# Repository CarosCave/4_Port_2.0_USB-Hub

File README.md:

# 4_Port_2.0_USB-Hub
I made a 4 port 2.0 USB-Hub with an exar XR22404 Chip. I wanted to test the schematic for the USB-Chip to use it in a further project. Version 1 is up and running here. But the costs for one complete equipped PCB is about 60€. Now in V2.0 I decreased the costs to 28€ for the parts.

You will find the:
-  CAD-Files in the folder **KiCAD**
-  The manufacturing files in the folder **Gerber-files**
-  The PDF documents in the folder **PDF**
-  The licence files from CERN OHL v. 1.2 under **Licence**

Or you order the complete Project by my friends from Aisler B.V.. The will deliver the complete project incl. all parts (excl. the USB-Chip from Exar). You'll find the project under the following link:
https://aisler.net/DK1CMB/4-port-2-0-usb-hub/main-pcb

The USB-Chip is an Exar XR22404CG28TR-F.

## Licence:  
**Copyright Caroline Brix 2017.**  
This documentation describes Open Hardware and is licensed under the CERN OHL v. 1.2.
You may redistribute and modify this documentation under the terms of the CERN OHL v.1.2. (http://ohwr.org/cernohl). This documentation is distributed WITHOUT ANY EXPRESS OR IMPLIED WARRANTY, INCLUDING OF MERCHANTABILITY, SATISFACTORY QUALITY AND FITNESS FOR A PARTICULAR PURPOSE. Please see the CERN OHL v.1.2 for applicable conditions

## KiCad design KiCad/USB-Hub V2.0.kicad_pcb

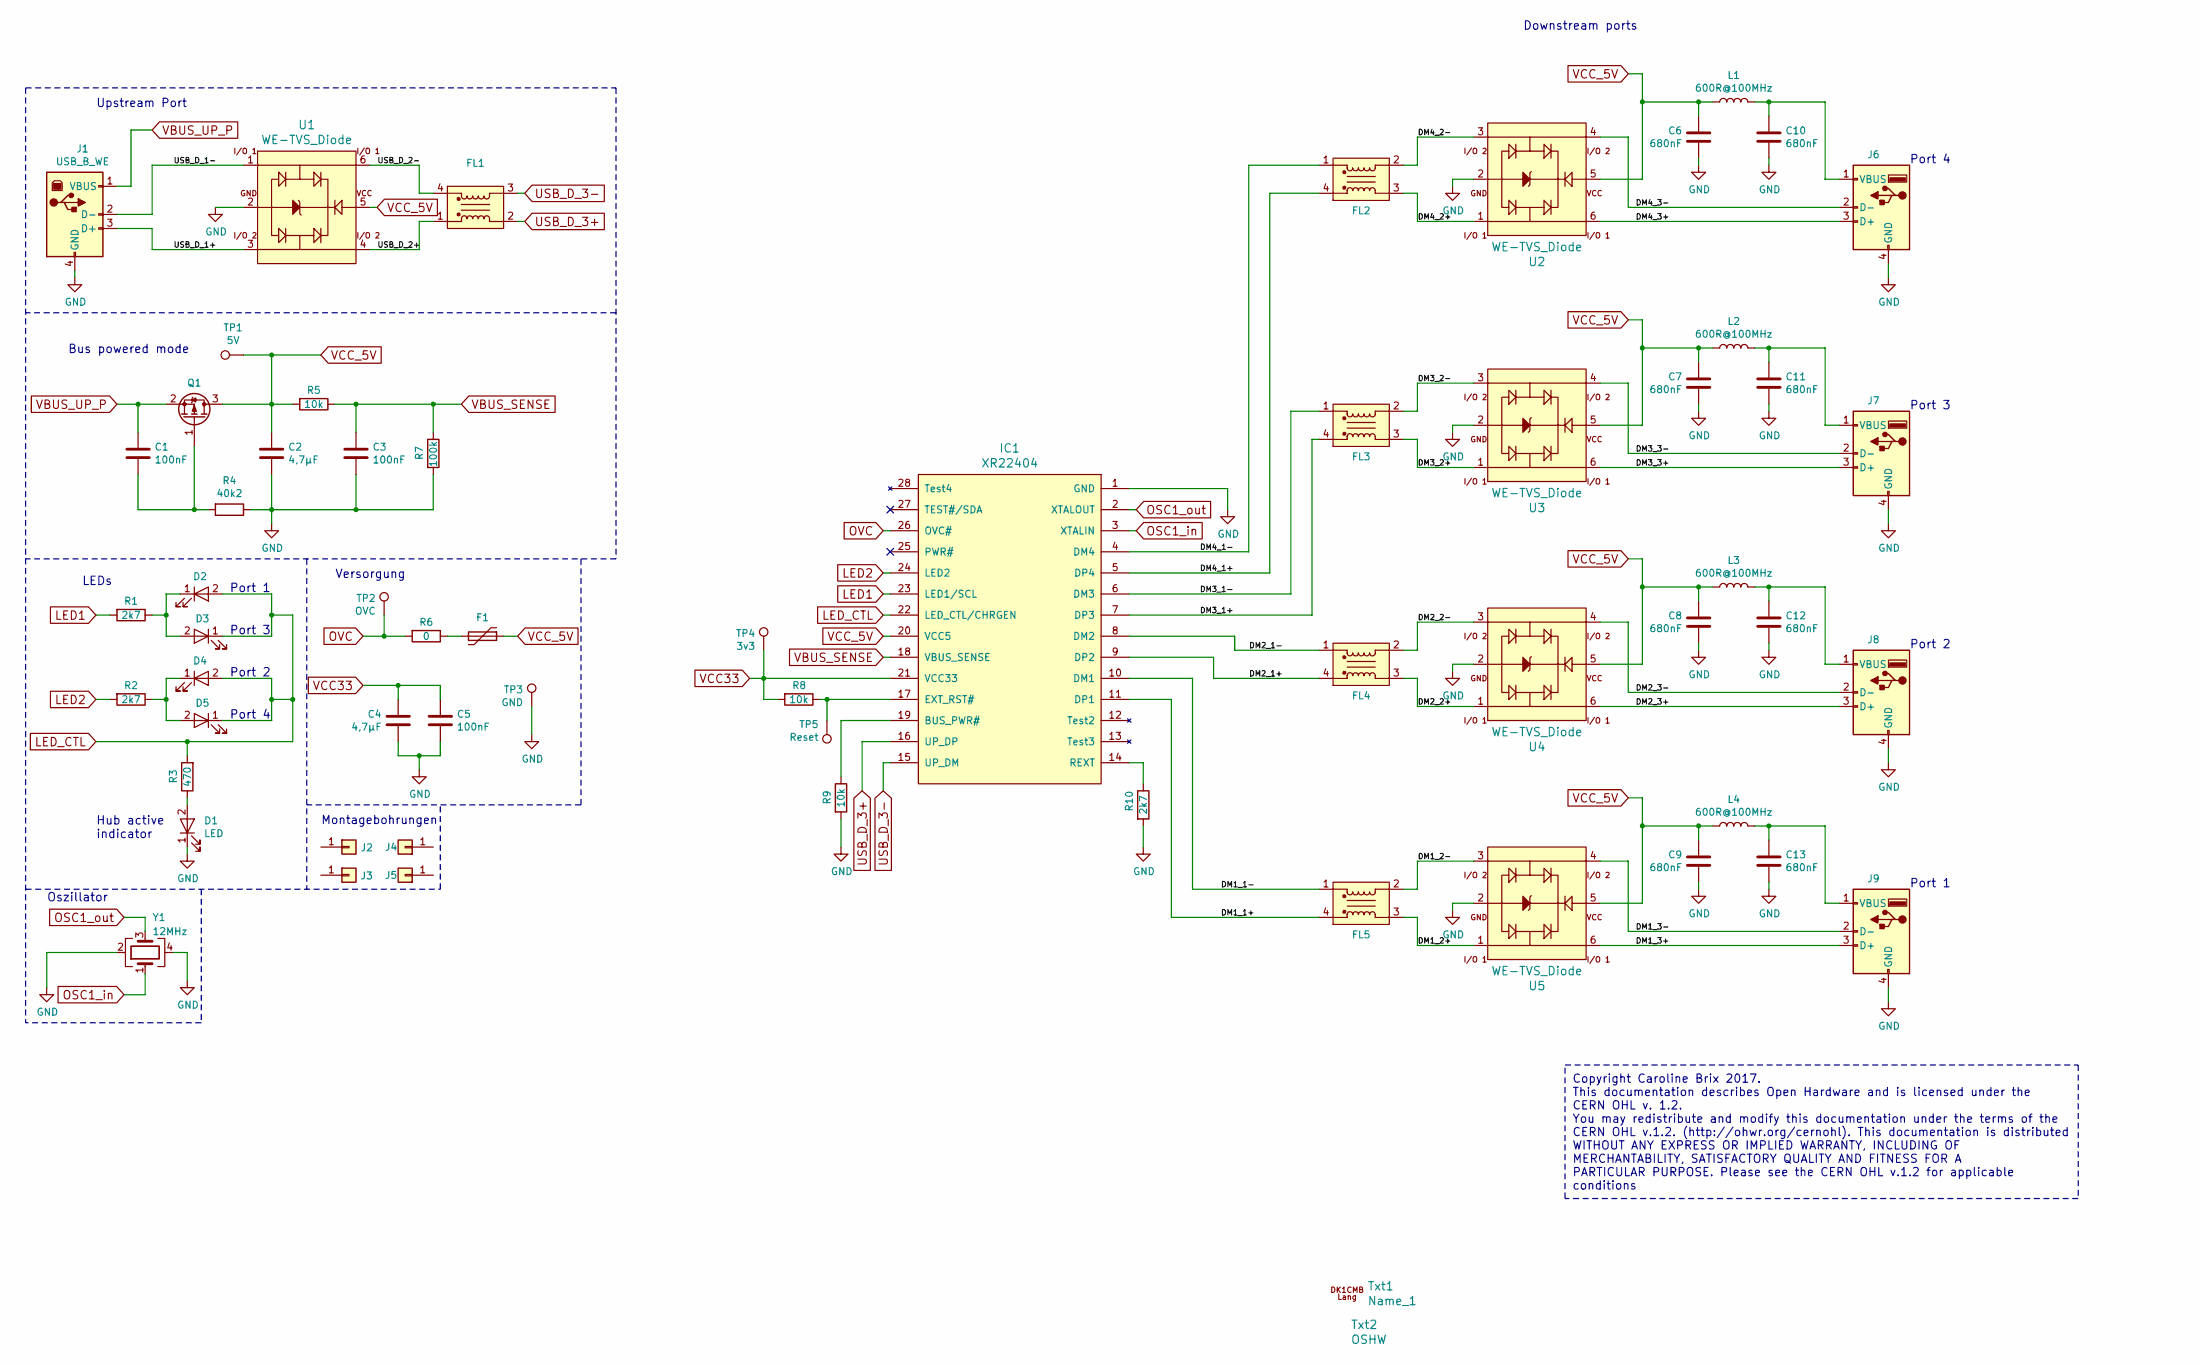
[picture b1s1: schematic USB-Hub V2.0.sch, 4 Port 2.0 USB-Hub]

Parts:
C1, C3, C5: 100nF; R_0805_HandSoldering
C2, C4: 4,7µF; R_0805_HandSoldering
C6, C7, C8, C9, C10, C11, C12, C13: 680nF; R_0805_HandSoldering
D1, D2, D3, D4, D5: LED; LED_0805_HandSoldering
F1: Polyfuse; R_1206_HandSoldering
FL1, FL2, FL3, FL4, FL5: EMI_Common_Mode_Line_Filter; WE-CNSW
IC1: XR22404
J1: USB_B_WE; USB_B_THT_WE
J2, J3, J4, J5: Conn_01x01; MountingHole_3.2mm_M3_Pad
J6, J7, J8, J9: USB_A_shielded; USB_A_shielded_WE
L1, L2, L3, L4: 600R@100MHz; R_0805_HandSoldering
Q1: NTR2101P; SOT-23
R1, R2, R10: 2k7; R_0805_HandSoldering
R3: 470; R_0805_HandSoldering
R4: 40k2; R_0805_HandSoldering
R5, R8, R9: 10k; R_0805_HandSoldering
R6: 0; R_0805_HandSoldering
R7: 100k; R_0805_HandSoldering
TP1: 5V; Test_Point_Pad_d3.0mm
TP2: OVC; Test_Point_Pad_d3.0mm
TP3: GND; Test_Point_Pad_d3.0mm
TP4: 3v3; Test_Point_Pad_d3.0mm
TP5: Reset; Test_Point_Pad_d3.0mm
Txt1: Name_1; Name_Lang
Txt2: OSHW; OSHW-Logo2_7.3x6mm_SilkScreen
U1, U2, U3, U4, U5: WE-TVS_Diode; SOT23-6L
Y1: 12MHz; Crystal_SMD_3225-4pin_3.2x2.5mm_HandSoldering

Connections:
/DM1_1+: FL5.4, IC1.11 (DP1)
/DM1_1-: FL5.1, IC1.10 (DM1)
/DM1_2+: FL5.3, U5.1
/DM1_2-: FL5.2, U5.3
/DM1_3+: J9.3 (D+), U5.6
/DM1_3-: J9.2 (D-), U5.4
/DM2_1+: FL4.4, IC1.9 (DP2)
/DM2_1-: FL4.1, IC1.8 (DM2)
/DM2_2+: FL4.3, U4.1
/DM2_2-: FL4.2, U4.3
/DM2_3+: J8.3 (D+), U4.6
/DM2_3-: J8.2 (D-), U4.4
/DM3_1+: FL3.4, IC1.7 (DP3)
/DM3_1-: FL3.1, IC1.6 (DM3)
/DM3_2+: FL3.3, U3.1
/DM3_2-: FL3.2, U3.3
/DM3_3+: J7.3 (D+), U3.6
/DM3_3-: J7.2 (D-), U3.4
/DM4_1+: FL2.4, IC1.5 (DP4)
/DM4_1-: FL2.1, IC1.4 (DM4)
/DM4_2+: FL2.3, U2.1
/DM4_2-: FL2.2, U2.3
/DM4_3+: J6.3 (D+), U2.6
/DM4_3-: J6.2 (D-), U2.4
/USB_D_1+: J1.3 (D+), U1.3
/USB_D_1-: J1.2 (D-), U1.1
/USB_D_2+: FL1.1, U1.4
/USB_D_2-: FL1.4, U1.6
GND: C2.2, C3.2, C4.1, C5.2, C6.1, C7.1, C8.1, C9.1, C10.2, C11.2, C12.2, C13.2, D1.1 (K), IC1.1 (GND), J1.4 (GND), J6.4 (GND), J7.4 (GND), J8.4 (GND), J9.4 (GND), R4.1, R7.2, R9.2, R10.2, TP3.1, U1.2, U2.2, U3.2, U4.2, U5.2, Y1.2, Y1.4
LED1: IC1.23 (LED1/SCL), R1.2
LED2: IC1.24 (LED2), R2.2
LED_CTL: D2.2 (A), D3.1 (K), D4.2 (A), D5.1 (K), IC1.22 (LED_CTL/CHRGEN), R3.2
unnamed: C1.2, Q1.1 (G), R4.2
unnamed: C10.1, J6.1 (VBUS), L1.2
unnamed: C11.1, J7.1 (VBUS), L2.2
unnamed: C12.1, J8.1 (VBUS), L3.2
unnamed: C13.1, J9.1 (VBUS), L4.2
unnamed: D1.2 (A), R3.1
unnamed: D2.1 (K), D3.2 (A), R1.1
unnamed: D4.1 (K), D5.2 (A), R2.1
unnamed: F1.2, R6.1
unnamed: IC1.14 (REXT), R10.1
unnamed: IC1.17 (EXT_RST#), R8.1, TP5.1
unnamed: IC1.19 (BUS_PWR#), R9.1
OSC1_in: IC1.3 (XTALIN), Y1.1
OSC1_out: IC1.2 (XTALOUT), Y1.3
OVC: IC1.26 (OVC#), R6.2, TP2.1
USB_D_3+: FL1.2, IC1.16 (UP_DP)
USB_D_3-: FL1.3, IC1.15 (UP_DM)
VBUS_SENSE: C3.1, IC1.18 (VBUS_SENSE), R5.1, R7.1
VBUS_UP_P: C1.1, J1.1 (VBUS), Q1.2 (S)
VCC33: C4.2, C5.1, IC1.21 (VCC33), R8.2, TP4.1
VCC_5V: C2.1, C6.2, C7.2, C8.2, C9.2, F1.1, IC1.20 (VCC5), L1.1, L2.1, L3.1, L4.1, Q1.3 (D), R5.2, TP1.1, U1.5, U2.5, U3.5, U4.5, U5.5

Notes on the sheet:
Bus powered mode
Port 1
Port 3
Port 2
Port 4
LEDs
Hub active indicator
Oszillator
Versorgung
Downstream ports
Port 3
Montagebohrungen
Upstream Port
Copyright Caroline Brix 2017. This documentation describes Open Hardware and is licensed under the CERN OHL v. 1.2. You may redistribute and modify this documentation under the terms of the CERN OHL v.1.2. (http://ohwr.org/cernohl). This documentation is distributed WITHOUT ANY EXPRESS OR IMPLIED W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

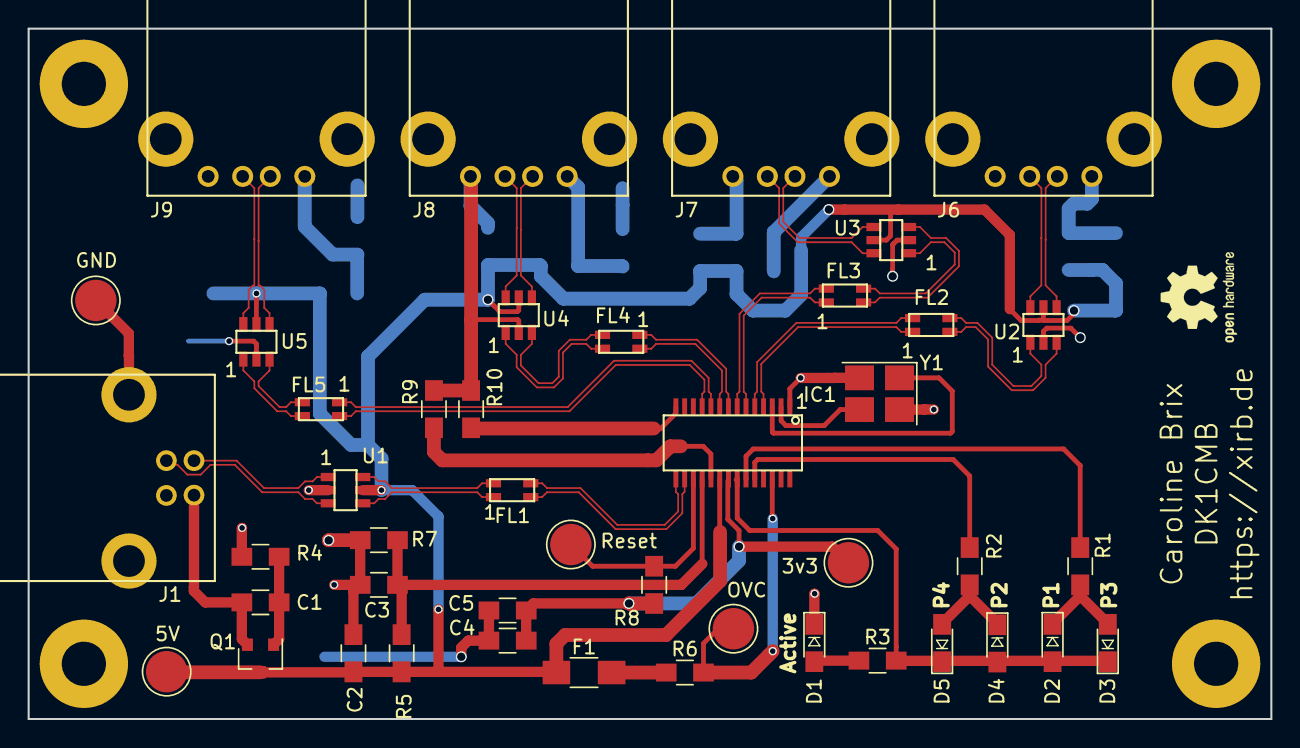
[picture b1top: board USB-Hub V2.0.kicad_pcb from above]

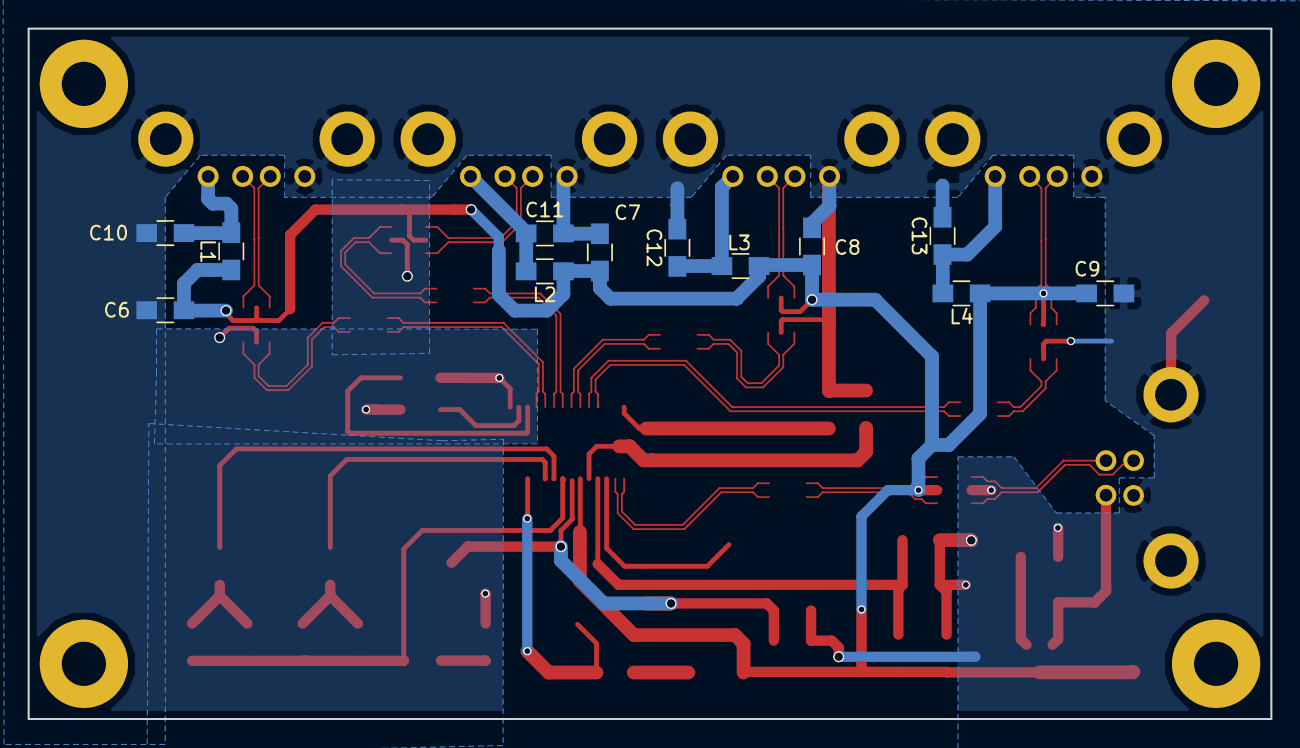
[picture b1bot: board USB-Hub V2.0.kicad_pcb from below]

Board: 2 copper layers, 90.0 x 50.0 mm, 62 parts (12 on the bottom side), 53 nets.

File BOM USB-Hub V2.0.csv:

ID;Bezeichner;Gehäuse;Stückzahl;Bezeichnung;Hersteller;Hersteller-Teilenummer;Mouser-Bestellnummer;Digikey-Bestellnummer;Preis Mouser;;Preis Digikey;;Datenblatt;Identifier;Case;Pieces;Description;Manufacturer;Manufacturer part number;Mouser part number;Digikey part number;Costs Mouser;;Costs Digikey;;Datasheet1;IC1;SSOP-28;1;USB-IC USB 2.0 4-Port Hub;Exar;XR22404CG28TR-F;701-XR22404CG28TR-F;nA; 2,02 € ; 2,02 € ;; -   € ;http://www.mouser.com/ds/2/146/XR22404-1006299.pdf2;J1;USB B;1;USB_B_WE;Wurth;61400416121;710-61400416121;732-2108-ND; 1,20 € ; 1,20 € ; 1,20 € ; 1,20 € ;http://katalog.we-online.de/em/datasheet/61400416121.pdf3;J6,J7,J8,J9;USB A;4;USB_A_shielded;Wurth;614004160211;710-614004160211;732-8248-ND; 1,50 € ; 6,00 € ; 1,48 € ; 5,92 € ;http://www.mouser.com/ds/2/445/wurth_08212017_614004160211-1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4;C1,C3,C5;SMD 0805;3;100nF;Wurth;885012207072;710-885012207072;732-8061-1-ND; 0,06 € ; 0,18 € ; 0,09 € ; 0,27 € ;5;C2,C4;SMD 0805;2;4,7µF;Vishay;VJ0805G475KXYTW1BC;77-VJ0805G475KXYTBC;-; 0,09 € ; 0,17 € ;; -   € ;;;;;;Taiyo;TMK212BJ475KG-T;-;587-1782-1-ND;;; 0,24 € ; 0,48 € ;6;C6,C7,C8,C9,C10,C11,C12,C13;SMD 0805;8;680nF;Kemet;C0805C684K4RACTU;80-C0805C684K4R;399-9267-1-ND; 0,17 € ; 1,36 € ; 0,17 € ; 1,36 € ;7;F1;SMD 1206;1;Polyfuse;Eaton;PTS120615V050;504-PTS120615V050;283-3140-1-ND; 0,26 € ; 0,26 € ; 0,27 € ; 0,27 € ;8;FL1,FL2,FL3,FL4,FL5;1206;5;EMI Common Mode Filter;Wurth;744232090;710-744232090;732-1469-1-ND; 1,12 € ; 5,60 € ; 1,12 € ; 5,60 € ;http://www.mouser.com/ds/2/445/744232090-538468.pdf9;L1,L2,L3,L4;SMD 0805;4;600R@100MHz;Wurth;74279204;710-74279204;732-1620-1-ND; 0,19 € ; 0,76 € ; 0,20 € ; 0,80 € ;http://www.mouser.com/ds/2/445/74279204-538332.pdf10;R1,R2,R10;SMD 0805;3;2k7;Vishay;CRCW08052K70JNEA;71-CRCW08052K70JNEA;541-2.7KACT-ND; 0,09 € ; 0,26 € ; 0,08 € ; 0,24 € ;11;R3;SMD 0805;1;470;Panasonic;ERJ-U06F4700V;667-ERJ-U06F4700V;-; 0,23 € ; 0,23 € ;; -   € ;;;;;;Bourns;CR0805-FX-4700ELF;-;CR0805-FX-4700ELFCT-ND;;; 0,08 € ; 0,08 € ;12;R4;SMD 0805;1;40k2;Vishay;CRCW080540K2FKEA;71-CRCW0805-40.2K-E3;541-40.2KCCT-ND; 0,09 € ; 0,09 € ; 0,08 € ; 0,08 € ;13;R5,R8,R9;SMD 0805;3;10k;Yageo;RC0805FR-0710KL;603-RC0805FR-0710KL;311-10.0KCRCT-ND; 0,09 € ; 0,26 € ; 0,08 € ; 0,24 € ;14;R6;SMD 0805;1;0;Yageo;RC0805JR-070RL;603-RC0805JR-070RL;311-0.0ARCT-ND; 0,09 € ; 0,09 € ; 0,08 € ; 0,08 € ;15;R7;SMD 0805;1;100k;Yageo;RC0805FR-07100KL;603-RC0805FR-07100KL;311-100KCRCT-ND; 0,09 € ; 0,09 € ; 0,08 € ; 0,08 € ;16;U1,U2,U3,U4,U5;SOT-23-6L;5;WE-TVS Diode;Wurth;82400102;710-82400102;732-4473-1-ND; 0,74 € ; 3,70 € ; 0,74 € ; 3,70 € ;http://www.mouser.com/ds/2/445/82400102-372913.pdf17;Y1;SMD 3225;1;12MHz;Diodes Incorporated;FL1200135;729-FL1200135;FL1200135 CT-ND; 0,72 € ; 0,72 € ; 0,59 € ; 0,59 € ;18;D1,D2,D3,D4,D5;SMD 0805;5;LED;Kingbright;APT2012SGC;604-APT2012SGC;754-1131-1-ND; 0,07 € ; 0,36 € ; 0,33 € ; 1,65 € ;19;Q1;SOT-23;1;MOSFET T1 60V PCH;ON Semiconductor;NVR5124PLT1G;863-NVR5124PLT1G;-; 0,37 € ; 0,37 € ;; -   € ;;;;;MOSFET P-CH 60V 1.8A CPH3;ON Semiconductor;CPH3351-TL-W;-;CPH3351-TL-WOSCT-ND;; -   € ; 0,41 € ; -   € ;20;J2,J3,J4,J5;3.2mm;4;Mounting Hole;;;;;;;;;;;;;;;;;;Netto; 23,69 € ;; 22,64 € ;;;;;;;;;;Brutto; 28,19 € ;; 26,94 € ;;;;;;;;;;;;;;;;;;;;;;;;;;;;;;;;;;;;;;;;

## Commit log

2017-10-25 no message
